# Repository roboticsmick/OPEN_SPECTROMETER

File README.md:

# OPEN_SPECTROMETER

This library allows you to use the Ocean Optics ST-VIS range of spectrometers using a Raspberry Pi Zerro 2W and a LCD display to view spectra using the Seabreeze API. This allows for a very small low power package that can easily be integrated into a small handheld device for field work. 

Lots of love to the the people working on keeping the PySeabreeze API alive. This let me get the Ocena Optic Spectrometer working on an ARM device. 

## Installing Pyseabreeze on Ubuntu PC for testing the spectrometer

```sh
cd
mkdir pysb
cd pysb
python3 -m venv --system-site-packages venv
source venv/bin/activate
pip install seabreeze[pyseabreeze]
seabreeze_os_setup
```

## Raspberry Pi Spectrometer Setup with Adafruit PiTFT 2.8"

Automated setup for a Raspberry Pi Zero 2 W with Ubuntu 22.04 Server LTS, Adafruit PiTFT 2.8" display, and pyseabreeze spectrometer integration.

## Hardware Requirements

- Raspberry Pi Zero 2 W
- Adafruit PiTFT 2.8" Resistive Touchscreen (Product ID: 1601)
- High-quality microSD card (128GB Samsung PRO Plus recommended)
- DS3231 RTC module (optional but recommended)
- Ocean Optics compatible spectrometer

## Initial Setup: Flash Ubuntu 22.04 Server LTS

### 1. Install Raspberry Pi Imager

```bash
sudo apt install rpi-imager
```

### 2. Flash the Operating System

**Hardware Configuration:**
- **Device:** Raspberry Pi Zero 2 W
- **OS:** Ubuntu 22.04 Server LTS
- **Storage:** Use a high-quality microSD card (don't skimp on quality)

**Imager Settings:**
1. Click `Edit Settings` before flashing
2. **General Tab:**
   - Hostname: `rpi`
   - Username: `pi`
   - Password: `spectro`
   - Configure wireless LAN: ✓
     - SSID: Your WiFi network name (mobile hotspot recommended for field use)
     - Password: Your WiFi password
     - Wireless LAN country: `AU` (or your country)
   - Set locale settings: ✓
     - Timezone: `Australia/Brisbane` (or your timezone)
     - Keyboard layout: `US`
3. **Services Tab:**
   - Enable SSH: ✓ (Use password authentication)
4. Click `Save`
5. Confirm OS customization settings when prompted
6. Flash the image to your microSD card

## First Boot and Connection

### 1. Initial Boot
- Enable your mobile phone hotspot (if using mobile hotspot for WiFi)
- Insert the flashed microSD card into the Raspberry Pi
- Power on the Raspberry Pi
- Wait for the device to connect to your WiFi network

### 2. Find the Pi's IP Address

**Option A: Using hostname (if available)**
```bash
ping rpi.local
```

**Option B: Network scan (if hostname doesn't work)**
```bash
# Check your laptop's IP address when connected to the same network
ifconfig
# Look for your interface (e.g., wlp3s0) and note the network
# Example: inet 10.119.124.83 means network is 10.119.124.0/24

# Scan the network
nmap -sn 10.119.124.0/24
```

### 3. SSH into the Raspberry Pi
```bash
ssh pi@<IP_ADDRESS>
```
Enter password: `spectro`

**Note:** Both your laptop and Raspberry Pi must be on the same network for SSH to work.

## Adding Additional WiFi Networks (Optional)

If you need to add more WiFi networks after initial setup:

1. Insert the microSD card into your computer
2. Navigate to the boot partition and edit the network configuration:
   ```bash
   sudo nano /path/to/boot/50-cloud-init.yaml
   ```
3. Add additional networks to the configuration:
   ```yaml
   network:
       version: 2
       wifis:
           renderer: networkd
           wlan0:
               access-points:
                   existing_network:
                       password: existing_password
                   new_network:
                       password: new_password
               dhcp4: true
               optional: true
   ```
4. Save and safely eject the microSD card
5. Reinsert into the Pi and power on

## Automated Setup

### 1. Download and Run the Setup Script

```bash
# Download the setup script
wget https://raw.githubusercontent.com/yourusername/yourrepo/main/setup_ada.sh

# Make it executable
chmod +x setup_ada.sh

# Run the setup (requires sudo)
sudo ./setup_ada.sh
```

### 2. What the Setup Script Does

The automated setup script handles:

- **System Configuration:**
  - System package updates and installation
  - Swap file configuration (2GB)
  - SPI and I2C interface enabling
  - User group permissions for hardware access

- **Display Setup:**
  - Adafruit PiTFT 2.8" driver installation and configuration
  - Console cursor control permissions for application use
  - Display rotation and framebuffer configuration

- **Python Environment:**
  - Virtual environment creation (`~/pysb-app/pysb_venv/`)
  - Integrated package installation (no separate requirements.txt needed):
    - numpy, pyusb (core dependencies)
    - matplotlib, pygame, pygame-menu (UI)
    - spidev, RPi.GPIO, rpi-lgpio (hardware interfaces)
    - seabreeze[pyseabreeze] (spectrometer support)

- **Hardware Configuration:**
  - DS3231 RTC module setup (if connected)
  - Seabreeze udev rules for spectrometer access
  - Terminal and bash improvements

### 3. Reboot Required

After the setup script completes:

```bash
sudo reboot
```

**Important:** The reboot is required for display drivers, hardware interfaces, and user permissions to take full effect.

## Running Your Application

After reboot, SSH back into the Pi and run your application:

```bash
# Navigate to project directory
cd ~/pysb-app

# Activate the virtual environment
source pysb_venv/bin/activate

# Run your application
python3 main.py
```

## Project File Structure

After setup, your project directory will contain:

```
~/pysb-app/
├── pysb_venv/           # Python virtual environment
├── main.py              # Your main application (copy this file to the Pi)
├── assets/              # Fonts, images, etc. (copy this directory to the Pi)
└── lib/                 # Additional libraries (if needed)
```

## Copying Your Application Files

You'll need to copy your `main.py` and `assets/` directory to the Pi:

```bash
# From your development machine, copy files to the Pi
scp main.py pi@<PI_IP>:~/pysb-app/
scp -r assets/ pi@<PI_IP>:~/pysb-app/
```

## Testing and Verification

### Test Spectrometer Connection
```bash
cd ~/pysb-app
source pysb_venv/bin/activate
python -m seabreeze.cseabreeze_backend ListDevices
```

### Test RTC (if installed)
```bash
sudo hwclock -r
```

### Test Display Cursor Control
```bash
# Disable cursor blinking (should work without permission errors)
echo 0 > /sys/class/graphics/fbcon/cursor_blink
```

### Test SPI Interface
```bash
ls -l /dev/spidev*
```

## Troubleshooting

### Common Issues

1. **SSH Connection Failed:**
   - Ensure both devices are on the same network
   - Try using IP address instead of hostname
   - Check that SSH is enabled in the Pi configuration

2. **Display Not Working:**
   - Ensure reboot was completed after setup
   - Check that the display is properly connected
   - Verify that the PiTFT installer completed successfully

3. **Spectrometer Not Detected:**
   - Check USB connection
   - Verify udev rules: `ls /etc/udev/rules.d/*ocean*`
   - Test with: `lsusb` to see if device is detected

4. **Python Package Import Errors:**
   - Ensure virtual environment is activated
   - Reinstall specific packages: `pip install <package_name>`

### Manual Fixes

If automatic setup fails for any component, you can run individual steps manually:

```bash
cd ~/pysb-app
source pysb_venv/bin/activate

# Reinstall specific Python packages
pip install matplotlib pygame pygame-menu

# Reinstall seabreeze
pip install seabreeze[pyseabreeze]

# Reset udev rules for seabreeze
sudo seabreeze_os_setup
```

## Hardware Notes

- **Power:** Use a quality power supply (2.5A recommended for Pi Zero 2 W with display)
- **microSD:** Use Class 10 or better, avoid cheap/counterfeit cards
- **Display:** Ensure proper connection of the PiTFT ribbon cable
- **RTC:** Connect DS3231 to I2C pins (SDA to GPIO 2, SCL to GPIO 3, VCC to 3.3V, GND to GND)

## Development Tips

- Use `screen` or `tmux` for persistent SSH sessions
- The setup script adds helpful bash aliases and history search
- Log files are typically in `/var/log/` for troubleshooting
- Use `dmesg` to check for hardware detection issues

## License

This setup is designed for educational and research purposes. Please ensure compliance with all applicable licenses for the software components used.

## Raspberry Pi breakout PCB

A custom PCB was built to add a USB-C power input, Blue Robotics waterproof power switch, real time clock (RTC) and battery, leak sensor and button inputs. An I2C and UART breakout was also added just for fun.

This complete schematic and board design can be found in the PCB folder. 

Leak sensor is based on the Blue Robotics leak sensor and uses Blue Robotics SOS leak sensor probes.

RTC is based on Adafruit's I2C DS3231 module.

## Power Usage:

Using a 10000mAh battery pack, the Raspberry Pi and spectrometer setup for approximately 10 hours and 18 minutes under the current load conditions.

Current during spectrometer live feed: ~0.6A 
Voltage: 5.099V
Power consumption = Voltage × Current
Power consumption = 5.099V × 0.6A = 3.06W
Energy capacity = 10000mAh × 3.7V ÷ 1000 = 37Wh
Assuming a typical efficiency rate: 85%
Actual available energy = 37Wh × 0.85 = 31.45Wh
Runtime = Available energy ÷ Power consumption
Runtime = 31.45Wh ÷ 3.06W ≈ 10.3 hours

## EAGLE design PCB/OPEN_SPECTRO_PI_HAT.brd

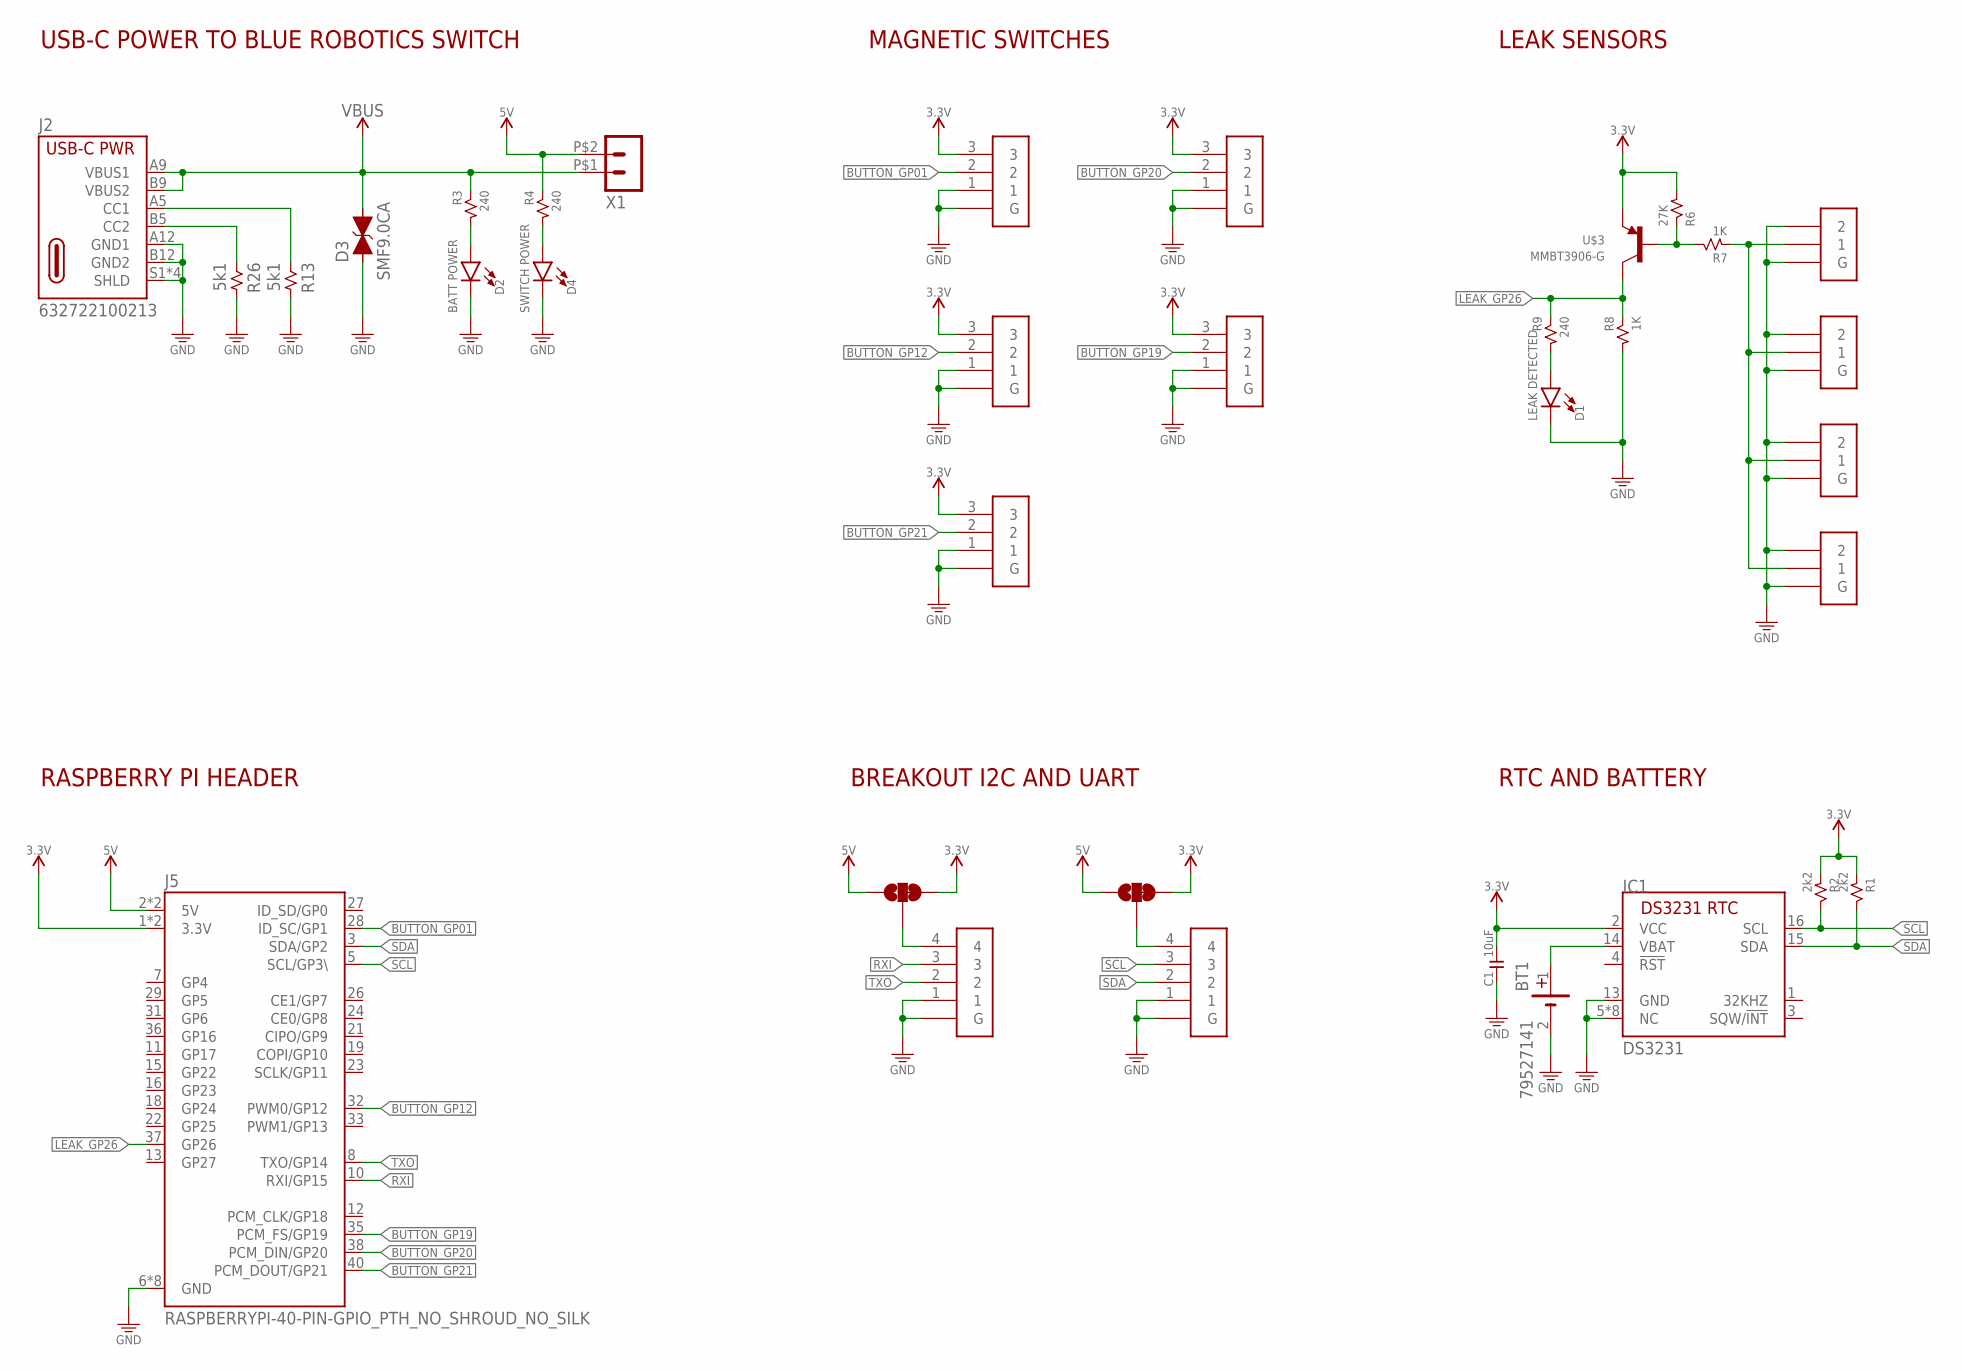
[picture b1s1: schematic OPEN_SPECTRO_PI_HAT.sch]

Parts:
BT1: 79527141
C1: 10uF; 0805
D1: LEAK DETECTED; 0805_LED
D2: BATT POWER; 0805_LED
D3: SMF9.0CA; SOD-123F-TVS
D4: SWITCH POWER; 0805_LED
IC1: DS3231/SO; SO16W
J2: 632722100213
J5: RASPBERRYPI-40-PIN-GPIO_PTH_NO_SHROUD_NO_SILK; 2X20_NOSILK
JP1, JP2: JUMPER-SMT_3_1-NC_TRACE_SILK; SMT-JUMPER_3_1-NC_TRACE_SILK
R1, R2: 2k2; 0805
R3, R4, R9: 240; 0805
R6: 27K; 0805
R7, R8: 1K; 0805
R13, R26: 5k1; 0805
U$1, U$2, U$5, U$6: JST-GH-2SIDE; JST-GH-SIDE-2
U$3: MMBT3906-G; SOT23-3_GENERIC
U$4, U$11, U$12, U$14, U$15: JST-GH-3SIDE; JST-GH-SIDE-3
U$7, U$8: JST-GH-4SIDE; JST-GH-SIDE-4
X1: MICRO-FIT_02P43650-0200; 43650-0200

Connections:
3.3V: C1.1, IC1.2 (VCC), J5.1 (3.3V), J5.17 (3.3V), JP1.3, JP2.3, R1.2, R2.2, R6.2, U$3.3 (C), U$4.3, U$11.3, U$12.3, U$14.3, U$15.3
5V: J5.2 (5V), J5.4 (5V), JP1.1, JP2.1, R4.1, X1.P$2 (2)
BATT_LED: D2.A, R3.2
BUTTON_GP01: J5.28 (ID_SC/GP1), U$4.2
BUTTON_GP12: J5.32 (PWM0/GP12), U$11.2
BUTTON_GP19: J5.35 (PCM_FS/GP19), U$15.2
BUTTON_GP20: J5.38 (PCM_DIN/GP20), U$14.2
BUTTON_GP21: J5.40 (PCM_DOUT/GP21), U$12.2
CC1: J2.A5 (CC1), R13.1
CC2: J2.B5 (CC2), R26.1
GND: BT1.2 (-), C1.2, D1.C, D2.C, D3.A (C1), D4.C, IC1.5 (NC), IC1.6 (NC), IC1.7 (NC), IC1.8 (NC), IC1.9 (NC), IC1.10 (NC), IC1.11 (NC), IC1.12 (NC), IC1.13 (GND), J2.A12 (GND1), J2.B12 (GND2), J2.S1 (SHLD), J2.S2 (SHLD), J2.S3 (SHLD), J2.S4 (SHLD), J5.6 (GND), J5.9 (GND), J5.14 (GND), J5.20 (GND), J5.25 (GND), J5.30 (GND), J5.34 (GND), J5.39 (GND), R8.2, R13.2, R26.2, U$1.2, U$1.MECH1 (G), U$1.MECH2 (G), U$2.2, U$2.MECH1 (G), U$2.MECH2 (G), U$4.1, U$4.MECH1 (G), U$4.MECH2 (G), U$5.2, U$5.MECH1 (G), U$5.MECH2 (G), U$6.2, U$6.MECH1 (G), U$6.MECH2 (G), U$7.1, U$7.MECH1 (G), U$7.MECH2 (G), U$8.1, U$8.MECH1 (G), U$8.MECH2 (G), U$11.1, U$11.MECH1 (G), U$11.MECH2 (G), U$12.1, U$12.MECH1 (G), U$12.MECH2 (G), U$14.1, U$14.MECH1 (G), U$14.MECH2 (G), U$15.1, U$15.MECH1 (G), U$15.MECH2 (G)
LEAK_GP26: J5.37 (GP26), R8.1, R9.1, U$3.2 (E)
LEAK_SEN: R7.2, U$1.1, U$2.1, U$5.1, U$6.1
LK_BASE: R6.1, R7.1, U$3.1 (B)
LK_LED: D1.A, R9.2
unnamed: JP1.2, U$7.4
unnamed: JP2.2, U$8.4
unnamed: D4.A, R4.2
RTC_BATT: BT1.1 (+), IC1.14 (VBAT)
RXI: J5.10 (RXI/GP15), U$8.3
SCL: IC1.16 (SCL), J5.5 (SCL/GP3\), R2.1, U$7.3
SDA: IC1.15 (SDA), J5.3 (SDA/GP2), R1.1, U$7.2
TXO: J5.8 (TXO/GP14), U$8.2
V_USB: D3.C (C2), J2.A9 (VBUS1), J2.B9 (VBUS2), R3.1, X1.P$1 (1)

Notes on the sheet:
USB-C POWER TO BLUE ROBOTICS SWITCH
RASPBERRY PI HEADER
MAGNETIC SWITCHES
LEAK SENSORS
BREAKOUT I2C AND UART
RTC AND BATTERY

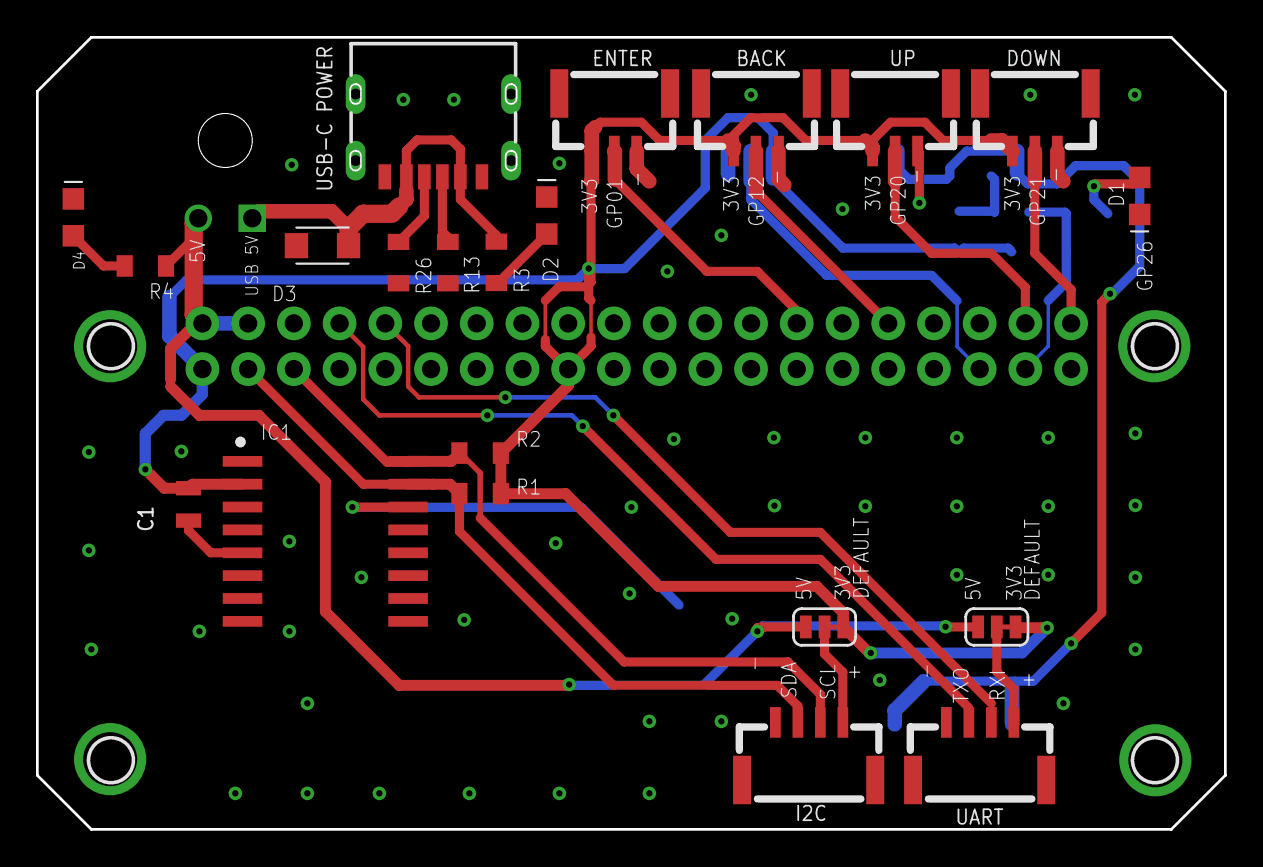
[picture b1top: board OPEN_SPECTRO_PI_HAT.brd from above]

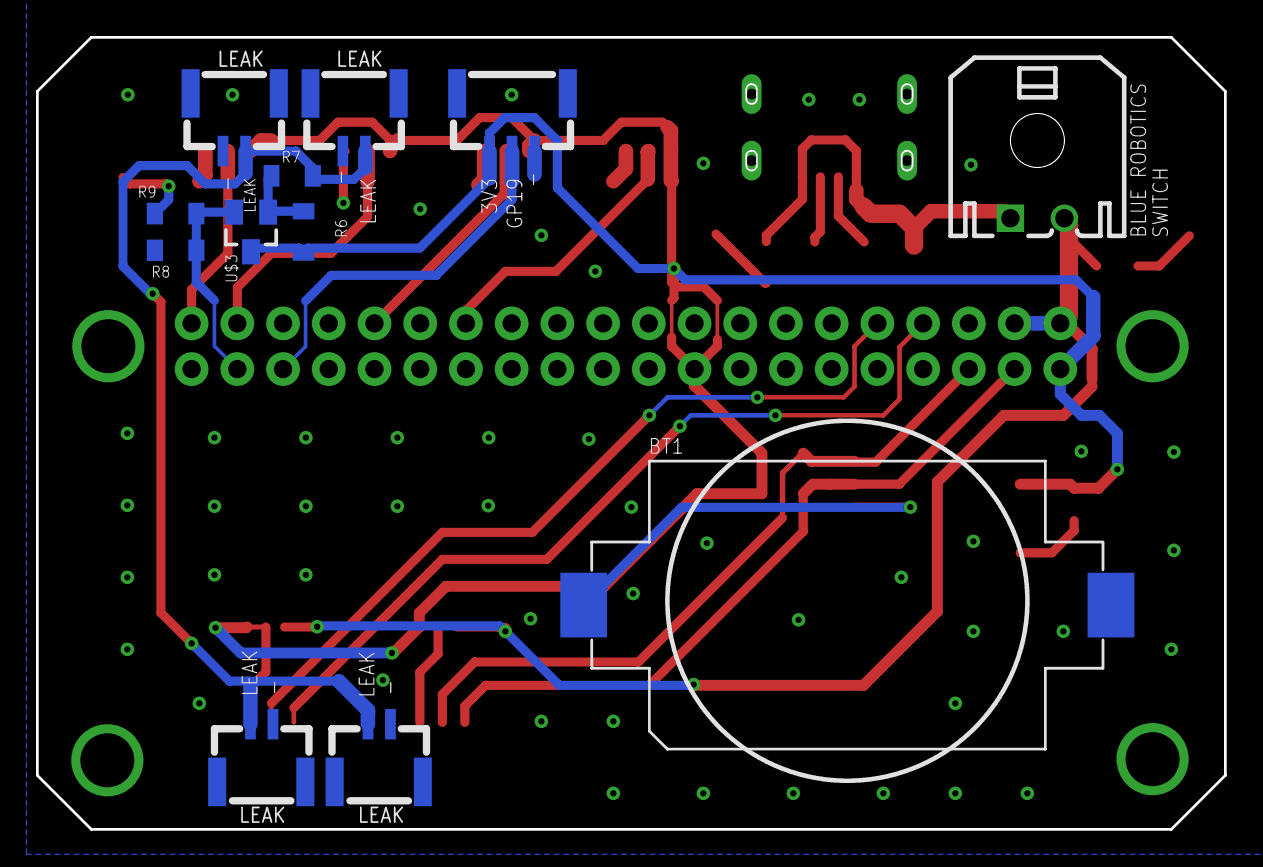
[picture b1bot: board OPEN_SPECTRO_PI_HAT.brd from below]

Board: 4 copper layers, 66.0 x 44.0 mm, 34 parts (12 on the bottom side), 24 nets.

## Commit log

2025-01-19 Rename disp_spec_plot.py to 1_3_INCH_WAVESHARE_LCD_PI_GLOBAL_SHUTTER_CAM/disp_spec_plot.py
2025-04-05 Rename main.py to Display HAT Mini/main.py
2025-05-09 Rename OPEN_SPECTRO_PI_HAT.brd to PCB/OPEN_SPECTRO_PI_HAT.brd
2025-05-09 Rename OPEN_SPECTRO_PI_HAT.sch to PCB/OPEN_SPECTRO_PI_HAT.sch
2025-05-09 Rename OPEN_SPECTRO_PI_HAT_SCHEMATIC.pdf to PCB/OPEN_SPECTRO_PI_HAT_SCHEMATIC.pdf

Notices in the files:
parts and their libraries:
SparkFun-Connectors: Licensing: Creative Commons ShareAlike 4.0 International - https://creativecommons.org/licenses/by-sa/4.0
_L_Symbols: CC-BY-SA
